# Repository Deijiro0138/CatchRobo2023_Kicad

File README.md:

# キャチロボ専用基板　仕様書
## マイコン
- Raspberry Pi Pico W x1

## 使用するアクチュエータ・センサ
- ステッピングモーター x2
- サーボ x3
- フォトリフレクタ x4
- 圧電スピーカー x1

## ピン配置
- GP0~2(サーボ)
- GP3(圧電スピーカー)
- GP6(モータ①Step),GP7(モータ①Dir)
- GP10(モータ②Step),GP11(モータ②Dir)
- GP12(遠隔非常停止)
- GP14(アナログマルチプレクサA),GP15(アナログマルチプレクサB)
- GP18~21(DIPスイッチ0-3)
- GP28(センサ読み取り用:ADC)

### MD・ステッピングモーター
使用するMDは[STSPIN220](https://akizukidenshi.com/catalog/g/gK-14790/)であり,
**Dirピン→方向**
**Stepピン→回転**
を指定する.

[17HS16-2004S1データシート](https://www.omc-stepperonline.com/download/17HS16-2004S1.pdf) <br>
[Amazon上でのサイトページ](https://www.amazon.co.jp/Nema-%E3%82%B9%E3%83%86%E3%83%83%E3%83%94%E3%83%B3%E3%82%B0%E3%83%A2%E3%83%BC%E3%82%BF-%E3%83%90%E3%82%A4%E3%83%9D%E3%83%BC%E3%83%A91-8%C2%B0-13Ncm-42x42x20mm/dp/B074Y4NP78/ref=asc_df_B074Y4NP78/?tag=jpgo-22&linkCode=df0&hvadid=265845994451&hvpos=&hvnetw=g&hvrand=9291562426356432587&hvpone=&hvptwo=&hvqmt=&hvdev=c&hvdvcmdl=&hvlocint=&hvlocphy=1009285&hvtargid=pla-456291539009&psc=1)

### アナログマルチプレクサ
アナログマルチプレクサはA,Bの2つの信号で読み取るチャンネルを切り替えられる.以下の真理値表を参照してほしい.

AはGP15,BはGP15に接続されている.**GP28のADC機能を用いて,チャンネルを切り替えながら周囲の障害物を検知する.** <br>
[CD4051BM96データシート](https://datasheet.lcsc.com/lcsc/1809261612_Texas-Instruments-CD4051BM96_C21379.pdf)

## 回路図
以下のファイルに現在の暫定版の回路図がある.
catchrobo2023/catchrobo2023.pdf

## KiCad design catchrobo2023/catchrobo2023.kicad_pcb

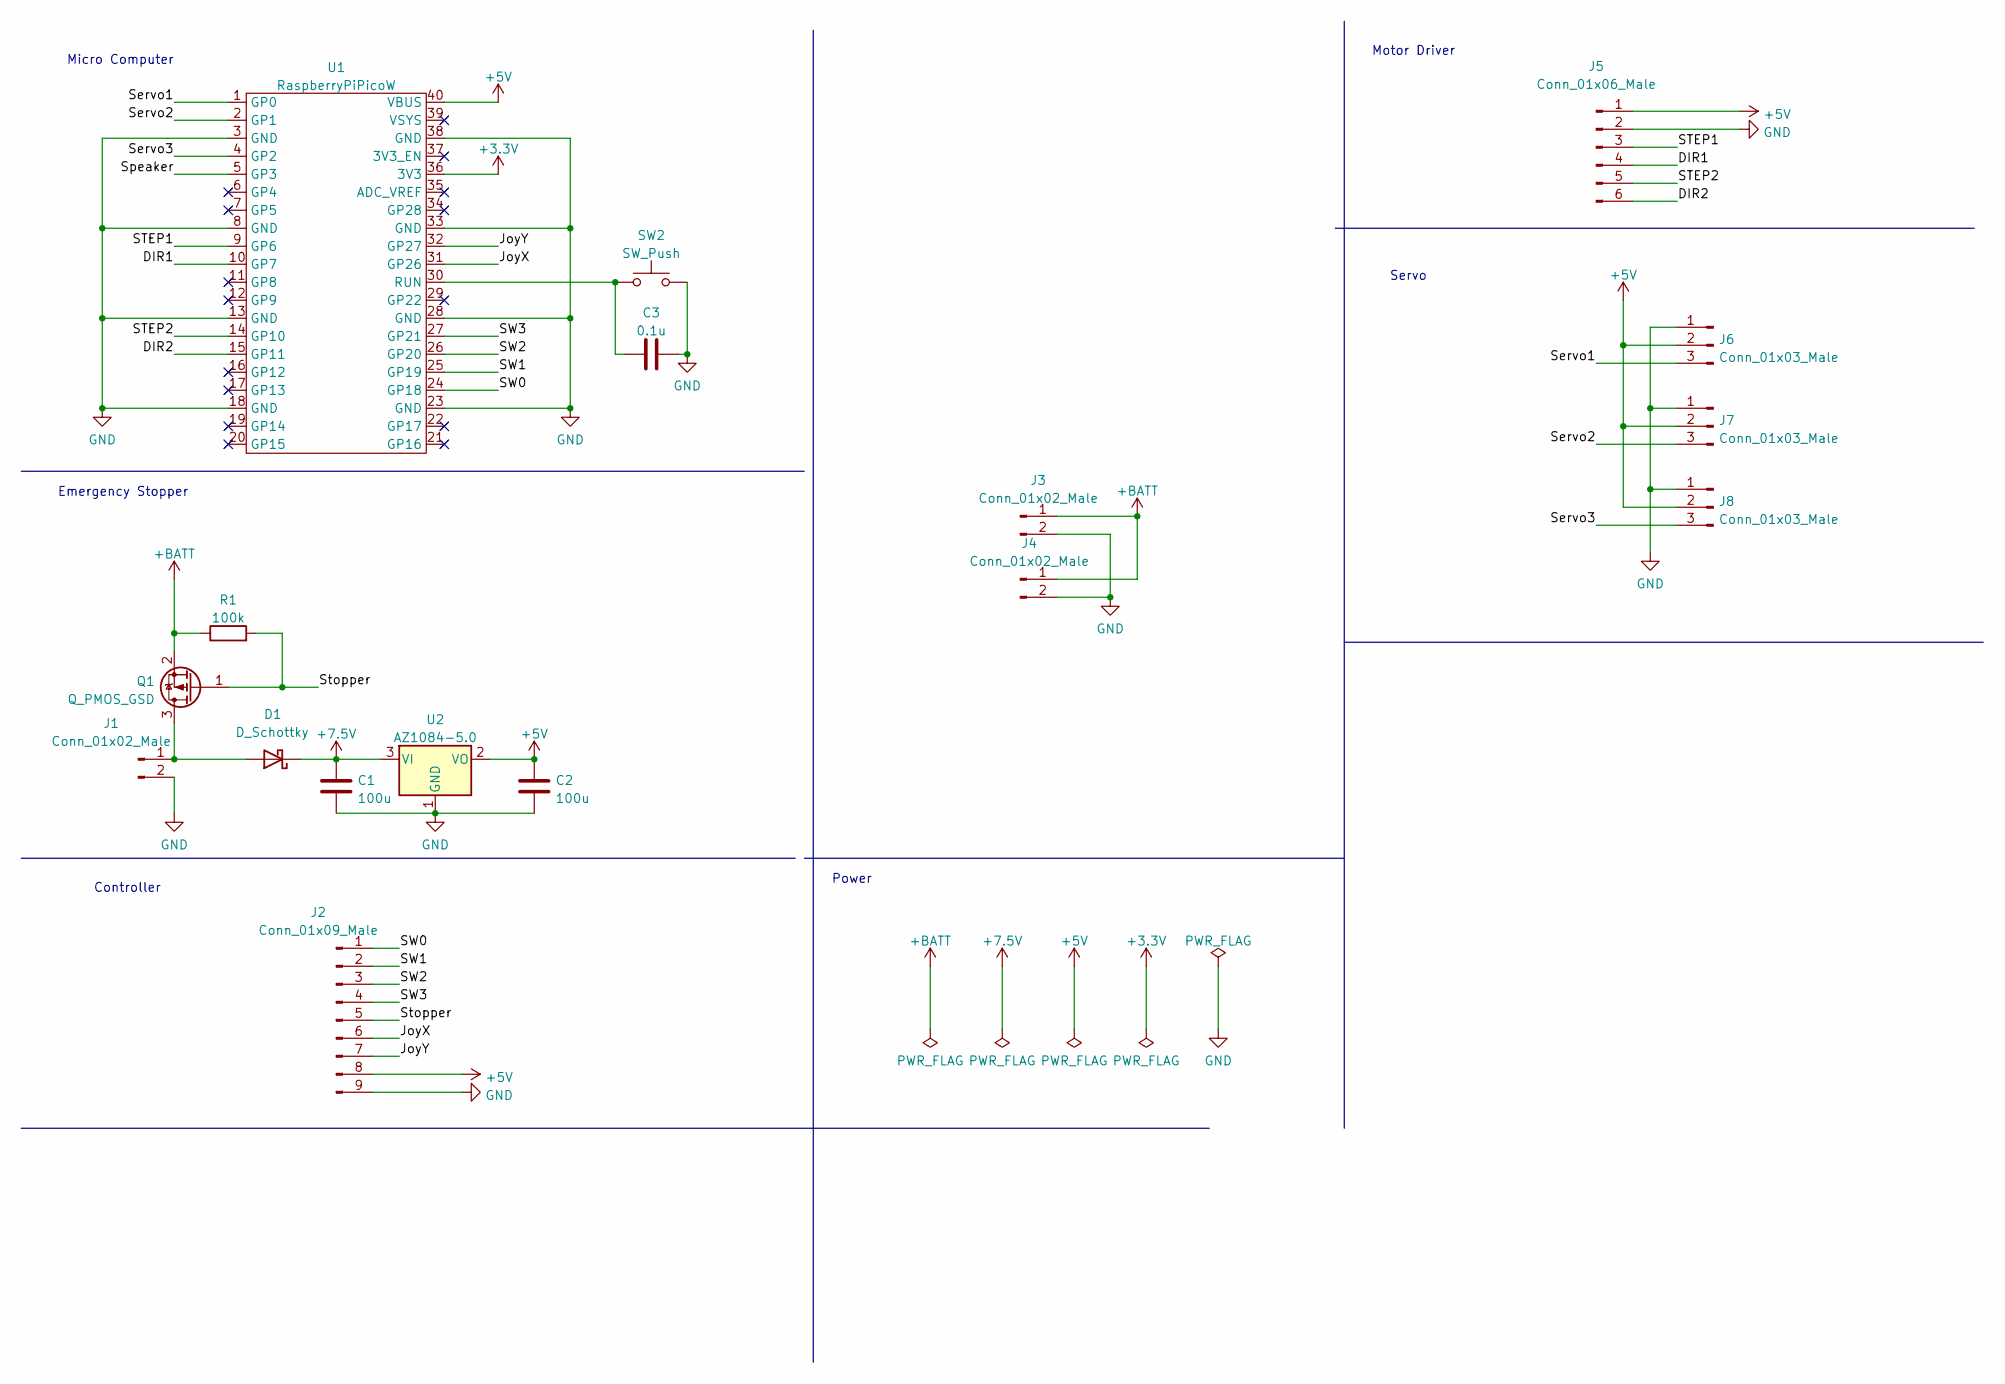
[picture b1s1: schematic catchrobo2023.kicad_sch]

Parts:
C1, C2: 100u; C_Radial_D5.0mm_H11.0mm_P2.00mm
C3: 0.1u; C_0603_1608Metric; LCSC C14663
D1: D_Schottky; D_SMA; LCSC C22452
J1, J3, J4: Conn_01x02_Male; JST_XH_S2B-XH-A_1x02_P2.50mm_Horizontal
J2: Conn_01x09_Male; JST_XH_S9B-XH-A-1_1x09_P2.50mm_Horizontal
J5: Conn_01x06_Male; JST_XH_S6B-XH-A_1x06_P2.50mm_Horizontal
J6, J7, J8: Conn_01x03_Male; PinHeader_1x03_P2.54mm_Vertical
Q1: Q_PMOS_GSD; SOT-23; LCSC C15127
R1: 100k; R_0603_1608Metric; LCSC C25803
SW2: SW_Push; TactSwitch
U1: RaspberryPiPicoW; RaspberryPiPico
U2: AZ1084-5.0; TO-252-2

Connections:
+3.3V: U1.36 (3V3)
+5V: C2.1, J2.8, J5.1, J6.2, J7.2, J8.2, U1.40 (VBUS), U2.2 (VO)
+7.5V: C1.1, D1.1 (K), U2.3 (VI)
+BATT: J3.1, J4.1, Q1.2 (S), R1.1
/DIR1: J5.4, U1.10 (GP7)
/DIR2: J5.6, U1.15 (GP11)
/JoyX: J2.6, U1.31 (GP26)
/JoyY: J2.7, U1.32 (GP27)
/STEP1: J5.3, U1.9 (GP6)
/STEP2: J5.5, U1.14 (GP10)
/SW0: J2.1, U1.24 (GP18)
/SW1: J2.2, U1.25 (GP19)
/SW2: J2.3, U1.26 (GP20)
/SW3: J2.4, U1.27 (GP21)
/Servo1: J6.3, U1.1 (GP0)
/Servo2: J7.3, U1.2 (GP1)
/Servo3: J8.3, U1.4 (GP2)
/Speaker: U1.5 (GP3)
/Stopper: J2.5, Q1.1 (G), R1.2
GND: C1.2, C2.2, C3.2, J1.2, J2.9, J3.2, J4.2, J5.2, J6.1, J7.1, J8.1, SW2.2, U1.3 (GND), U1.8 (GND), U1.13 (GND), U1.18 (GND), U1.23 (GND), U1.28 (GND), U1.33 (GND), U1.38 (GND), U2.1 (GND)
unnamed: C3.1, SW2.1, U1.30 (RUN)
unnamed: D1.2 (A), J1.1, Q1.3 (D)

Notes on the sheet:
Controller
Emergency Stopper
Motor Driver
Servo
Micro Computer
Power

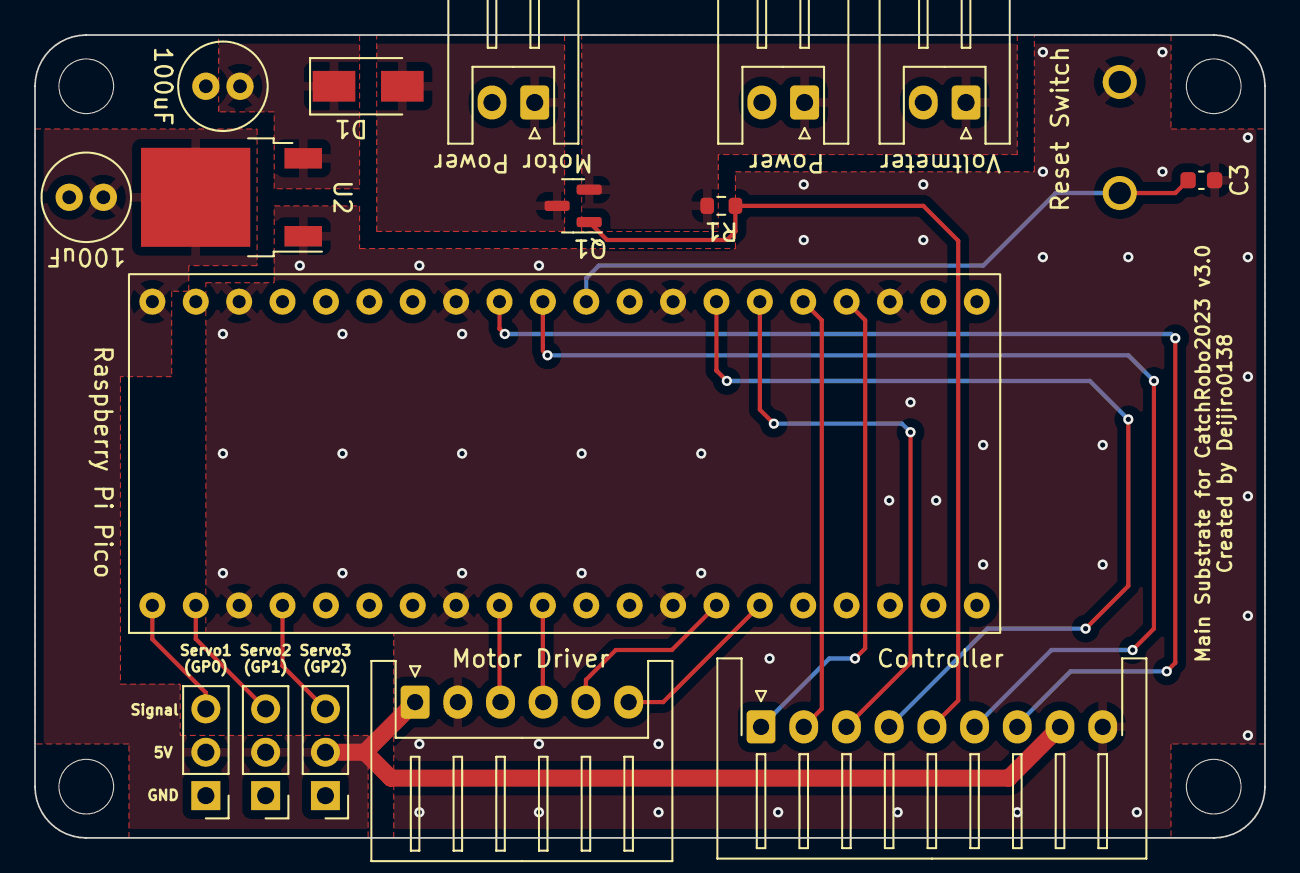
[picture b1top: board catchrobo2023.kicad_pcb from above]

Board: 2 copper layers, 72.0 x 47.0 mm, 17 parts (0 on the bottom side), 20 nets.

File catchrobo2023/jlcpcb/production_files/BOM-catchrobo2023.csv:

Comment,Designator,Footprint,LCSC
0.1u,C3,C_0603_1608Metric,C14663
Q_PMOS_GSD,Q1,SOT-23,C15127
D_Schottky,D1,D_SMA,C22452
100k,R1,R_0603_1608Metric,C25803
Conn_01x09_Male,J2,JST_XH_S9B-XH-A-1_1x09_P2.50mm_Horizontal,
100u,C1,C_Radial_D5.0mm_H11.0mm_P2.00mm,
Conn_01x02_Male,J3,JST_XH_S2B-XH-A_1x02_P2.50mm_Horizontal,
Conn_01x06_Male,J5,JST_XH_S6B-XH-A_1x06_P2.50mm_Horizontal,
Conn_01x03_Male,J6,PinHeader_1x03_P2.54mm_Vertical,
SW_Push,SW2,TactSwitch,
Conn_01x02_Male,J4,JST_XH_S2B-XH-A_1x02_P2.50mm_Horizontal,
AZ1084-5.0,U2,TO-252-2,
Conn_01x03_Male,J8,PinHeader_1x03_P2.54mm_Vertical,
Conn_01x03_Male,J7,PinHeader_1x03_P2.54mm_Vertical,
100u,C2,C_Radial_D5.0mm_H11.0mm_P2.00mm,
Conn_01x02_Male,J1,JST_XH_S2B-XH-A_1x02_P2.50mm_Horizontal,
RaspberryPiPicoW,U1,RaspberryPiPico,

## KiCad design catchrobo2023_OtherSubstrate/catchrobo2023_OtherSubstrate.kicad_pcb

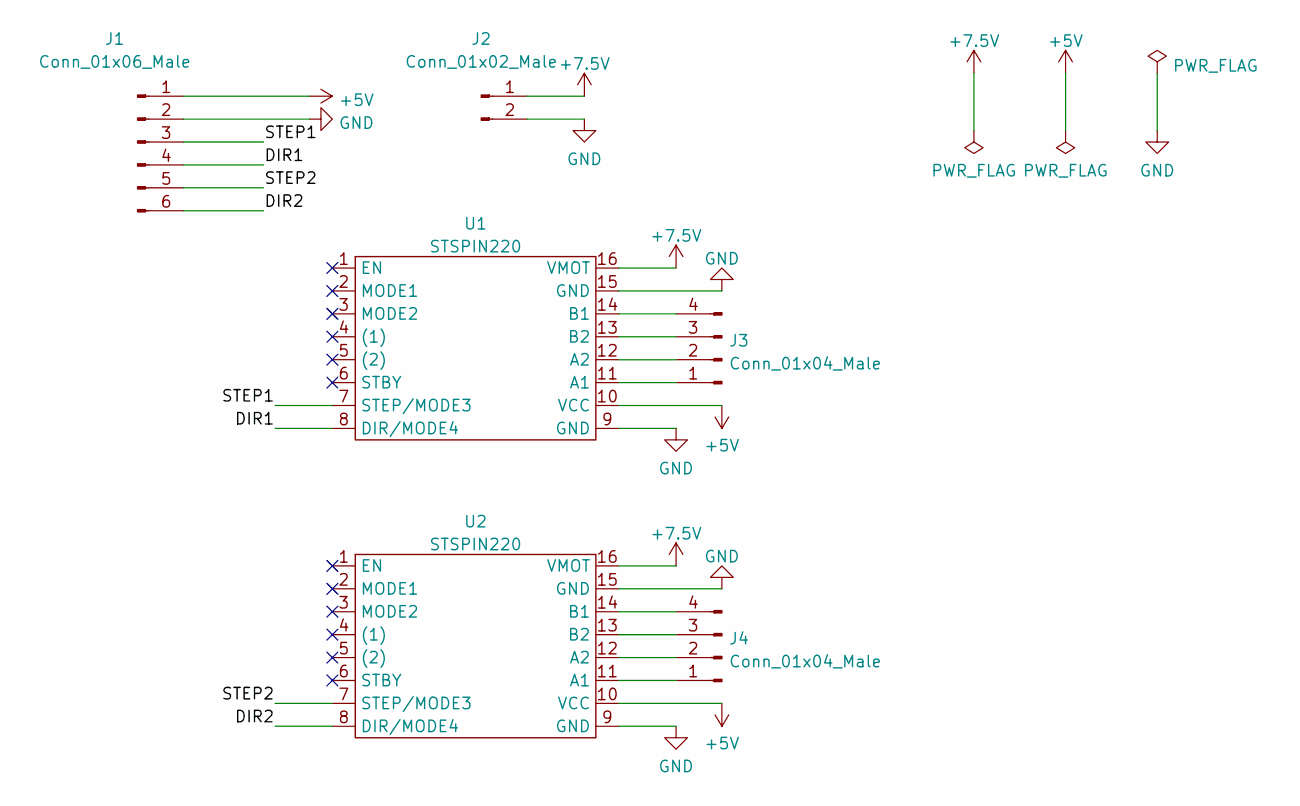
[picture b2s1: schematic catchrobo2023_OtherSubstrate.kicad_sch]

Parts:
J1: Conn_01x06_Male; JST_XH_S6B-XH-A_1x06_P2.50mm_Horizontal
J2: Conn_01x02_Male; JST_XH_S2B-XH-A-1_1x02_P2.50mm_Horizontal
J3, J4: Conn_01x04_Male; JST_XH_S4B-XH-A-1_1x04_P2.50mm_Horizontal
U1, U2: STSPIN220

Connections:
+5V: J1.1, U1.10 (VCC), U2.10 (VCC)
+7.5V: J2.1, U1.16 (VMOT), U2.16 (VMOT)
/DIR1: J1.4, U1.8 (DIR/MODE4)
/DIR2: J1.6, U2.8 (DIR/MODE4)
/STEP1: J1.3, U1.7 (STEP/MODE3)
/STEP2: J1.5, U2.7 (STEP/MODE3)
GND: J1.2, J2.2, U1.9 (GND), U1.15 (GND), U2.9 (GND), U2.15 (GND)
unnamed: J3.1, U1.11 (A1)
unnamed: J3.2, U1.12 (A2)
unnamed: J3.3, U1.13 (B2)
unnamed: J3.4, U1.14 (B1)
unnamed: J4.1, U2.11 (A1)
unnamed: J4.2, U2.12 (A2)
unnamed: J4.3, U2.13 (B2)
unnamed: J4.4, U2.14 (B1)

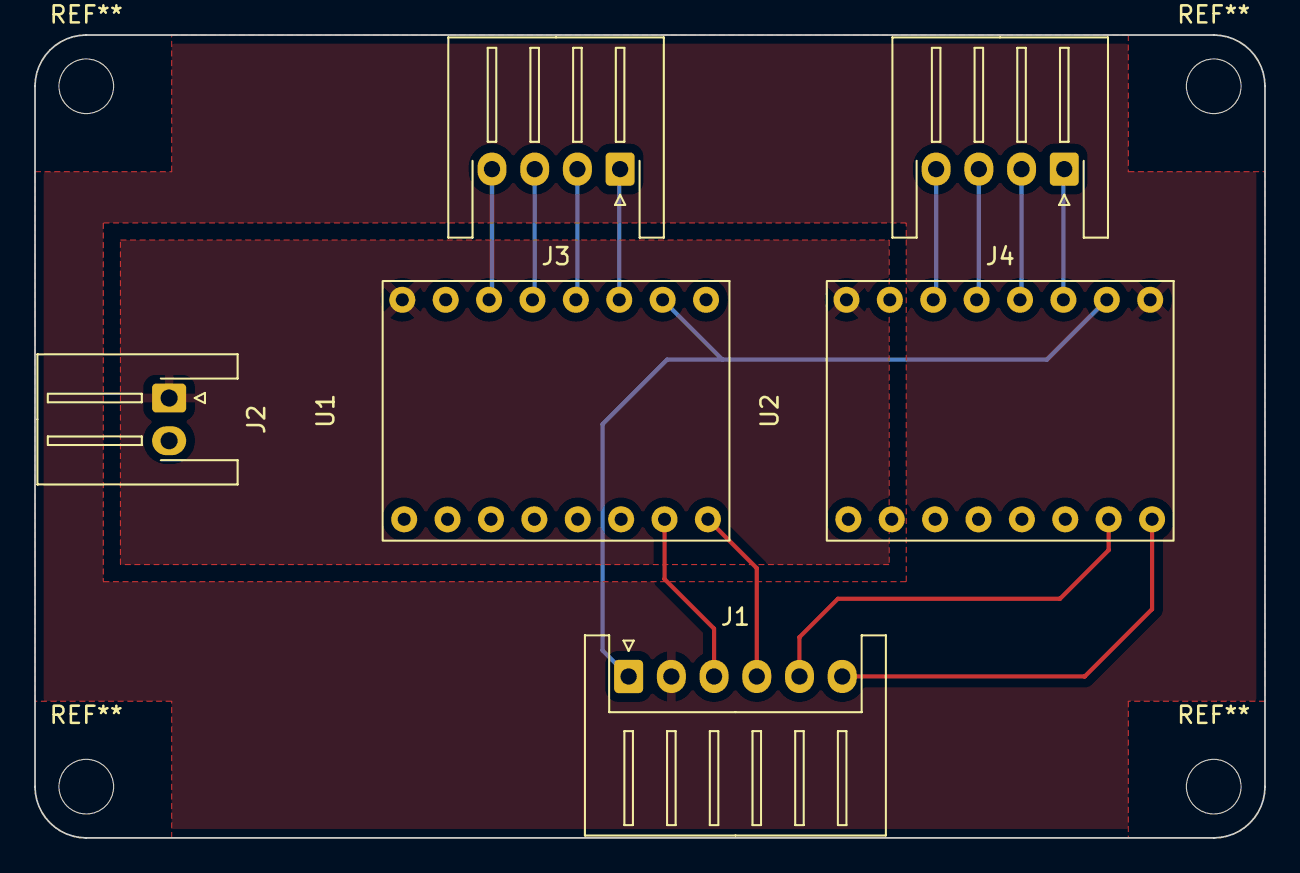
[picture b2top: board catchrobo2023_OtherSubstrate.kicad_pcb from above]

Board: 2 copper layers, 72.0 x 47.0 mm, 6 parts (0 on the bottom side), 15 nets.

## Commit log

2023-06-07 サーボ、MD、センサの回路図までは実装
2023-06-07 リレーまで追加
2023-06-11 緊急非常停止以外の回路図は完了
2023-06-13 フットプリントを一部選定
2023-06-13 README追加
2023-06-13 フットプリントの割り当て途中②
2023-06-14 回路図、部品選定が一旦終了
2023-06-14 遠隔非常停止に使用するリレーをFETに変更
2023-06-14 メイン基板作成途中
2023-06-15 部品配置一旦終わり
2023-06-15 部品配置完了！
2023-06-16 基板上のシルクを整備（ピン番号の表記など）
2023-06-16 READMEの更新
2023-06-16 フォトリフレクタの周辺を修正
2023-06-16 一旦、発注に必要なファイルも出力
2023-06-16 README.mdを更新
2023-06-16 README.mdに画像を追加
2023-06-16 READMEと画像を更新
2023-06-16 README更新
2023-06-16 製造ファイルまで出力
2023-06-16 ロゴの追加
2023-06-16 READMEに使用する画像を差し替え
2023-06-16 README修正
2023-06-17 DIPスイッチのシルクの向きを変更
2023-06-17 5V電源(XH)を追加
2023-06-17 MD用の基板を設計
2023-06-17 製造ファイルを出力
2023-07-15 コントローラ基板のプロジェクトを作成
2023-07-18 コントローラへの配線以外は完了
2023-07-26 Main基板の修正完了
2023-07-29 MDを修正
2023-07-29 メイン基板の製造ファイルを出力
2023-08-15 ちょっとしたアップデート
2023-08-15 pchFetによる電源スイッチを追加
2023-08-16 回収機基板設計完了
2023-08-16 輸送機の基板設計開始
2023-08-16 製造ファイルを作成
